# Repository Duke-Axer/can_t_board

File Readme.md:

**Jest to płytka (10 × 10 cm) z procesorem Cortex M0+, zaprojektowana do testów urządzeń komunikujących się przez różne interfejsy.**

## Główne cechy:

**Procesor:** ARM Cortex M0+
**Interfejsy komunikacyjne:**
- SWD (Serial Wire Debug) – programowanie i debugowanie
- SPI (Serial Peripheral Interface)
- UART (Universal Asynchronous Receiver/Transmitter)
- CAN (Controller Area Network)
- USB (Device mode)

**Zasilanie:**
- Wbudowana przetwornica AC/DC
- Zasilanie z gniazda 230 VAC
- Wbudowane napięcia wyjściowe: 5 V i 3.3 V

**Wymiary PCB:** 10 × 10 cm  
**Symulacje:** Przetwornica została zasymulowana w LTspice.  
/projekt  
  ├─ ltspice/         # Symulacje przetwornicy w LTspice  
  ├─ Lib_CAN/      	  # Biblioteka z modelami dla Kicad  
  ├─ BOM/             # Lista użytych footprintów  
  ├─ README.md        # Ten plik  
  └─ CAN_t_b.jpg      # Obraz z widoku 3D

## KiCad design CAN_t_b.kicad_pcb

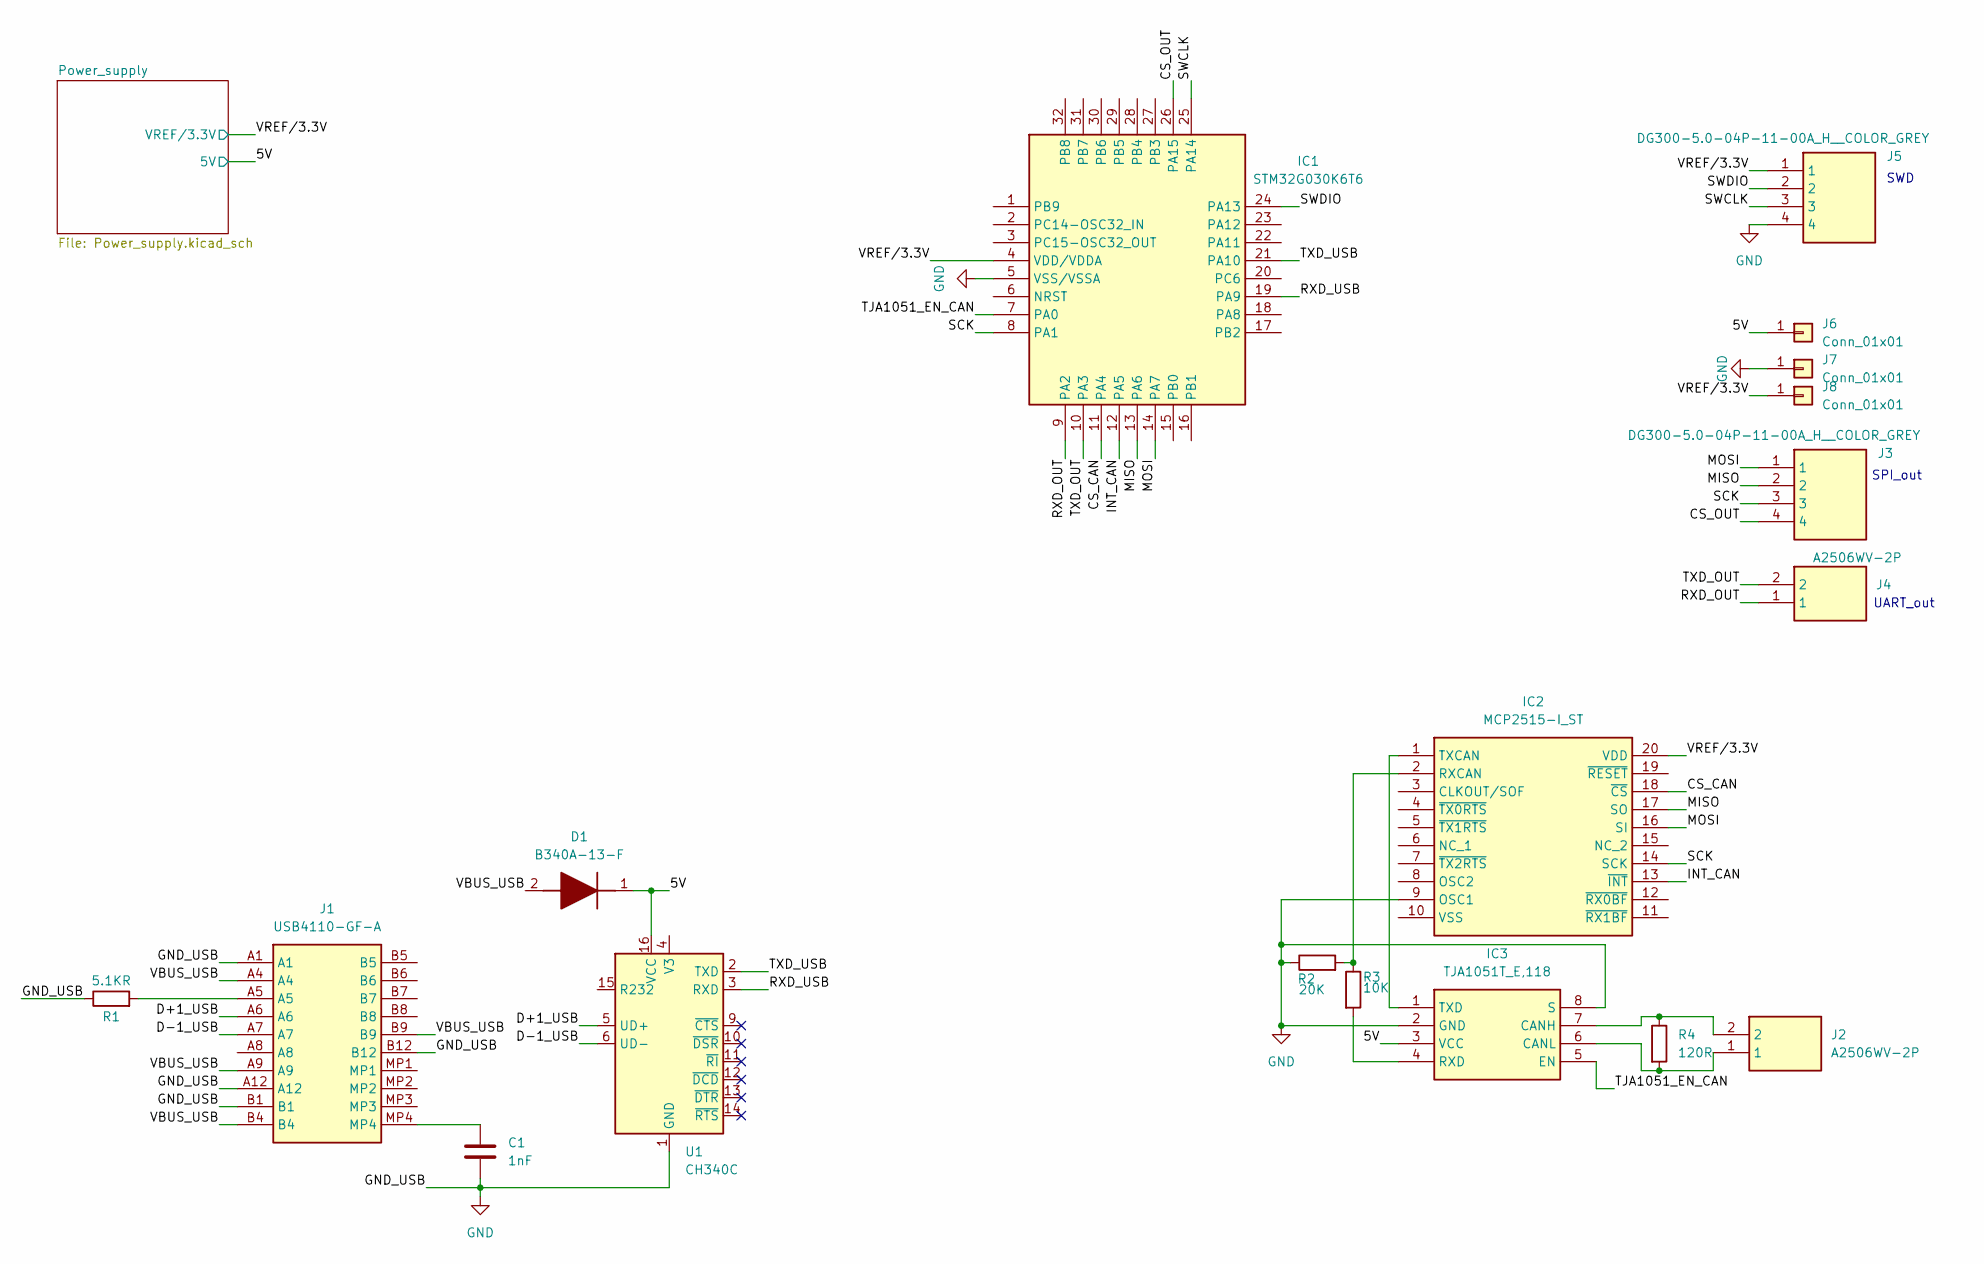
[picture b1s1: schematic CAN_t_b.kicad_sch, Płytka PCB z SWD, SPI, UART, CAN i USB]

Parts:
C1: 1nF; C_0201_0603Metric
D1: B340A-13-F; DIOM5226X240N; Manufacturer_Part_Number B340A-13-F
IC1: STM32G030K6T6; QFP80P900X900X160-32N; Manufacturer_Part_Number STM32G030K6T6
IC2: MCP2515-I_ST; SOP65P640X120-20N; Mouser Part Number 579-MCP2515-I/ST
IC3: TJA1051T_E,118; SOIC127P600X175-8N; Manufacturer_Part_Number TJA1051T/E,118
J1: USB4110-GF-A; USB4110GFA; Manufacturer_Part_Number USB4110-GF-A
J2, J4: A2506WV-2P; A2506WV2P; Manufacturer_Part_Number A2506WV-2P
J3, J5: DG300-5.0-04P-11-00A_H__COLOR_GREY; DG3005004P1100AHCOLORGREY; Manufacturer_Part_Number DG300-5.0-04P-11-00A(H) COLOR GREY
J6, J7, J8: Conn_01x01; PinHeader_1x01_P2.54mm_Vertical
R1: 5.1KR; R_0603_1608Metric
R2: 20K; R_0201_0603Metric
R3: 10K; R_0201_0603Metric
R4: 120R; R_0201_0603Metric
U1: CH340C; SOIC-16_3.9x9.9mm_P1.27mm

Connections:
/5V: D1.1 (K), IC3.3 (VCC), J6.1, U1.16 (VCC); also elsewhere on the board
/CS_CAN: IC1.11 (PA4), IC2.18 (~CS)
/CS_OUT: IC1.26 (PA15), J3.4
/D+1_USB: J1.A6, U1.5 (UD+)
/D-1_USB: J1.A7, U1.6 (UD-)
/INT_CAN: IC1.12 (PA5), IC2.13 (~INT)
/MISO: IC1.13 (PA6), IC2.17 (SO), J3.2
/MOSI: IC1.14 (PA7), IC2.16 (SI), J3.1
/RXD_OUT: IC1.9 (PA2), J4.1
/RXD_USB: IC1.19 (PA9), U1.3 (RXD)
/SCK: IC1.8 (PA1), IC2.14 (SCK), J3.3
/SWCLK: IC1.25 (PA14), J5.3
/SWDIO: IC1.24 (PA13), J5.2
/TJA1051_EN_CAN: IC1.7 (PA0), IC3.5 (EN)
/TXD_OUT: IC1.10 (PA3), J4.2
/TXD_USB: IC1.21 (PA10), U1.2 (TXD)
/VBUS_USB: D1.2 (A), J1.A4, J1.A9, J1.B4, J1.B9
/VREF/3.3V: IC1.4 (VDD/VDDA), IC2.20 (VDD), J5.1, J8.1; also elsewhere on the board
GND: C1.2, IC1.5 (VSS/VSSA), IC2.9 (OSC1), IC3.2 (GND), IC3.8 (S), J1.A1, J1.A12, J1.B1, J1.B12, J5.4, J7.1, R1.1, R2.1, U1.1 (GND); also elsewhere on the board
unnamed: C1.1, J1.MP4
unnamed: IC2.2 (RXCAN), R2.2, R3.1
unnamed: IC2.1 (TXCAN), IC3.1 (TXD)
unnamed: IC3.7 (CANH), J2.2, R4.1
unnamed: IC3.6 (CANL), J2.1, R4.2
unnamed: IC3.4 (RXD), R3.2
unnamed: J1.A5, R1.2

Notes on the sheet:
UART_out
SWD
SPI_out

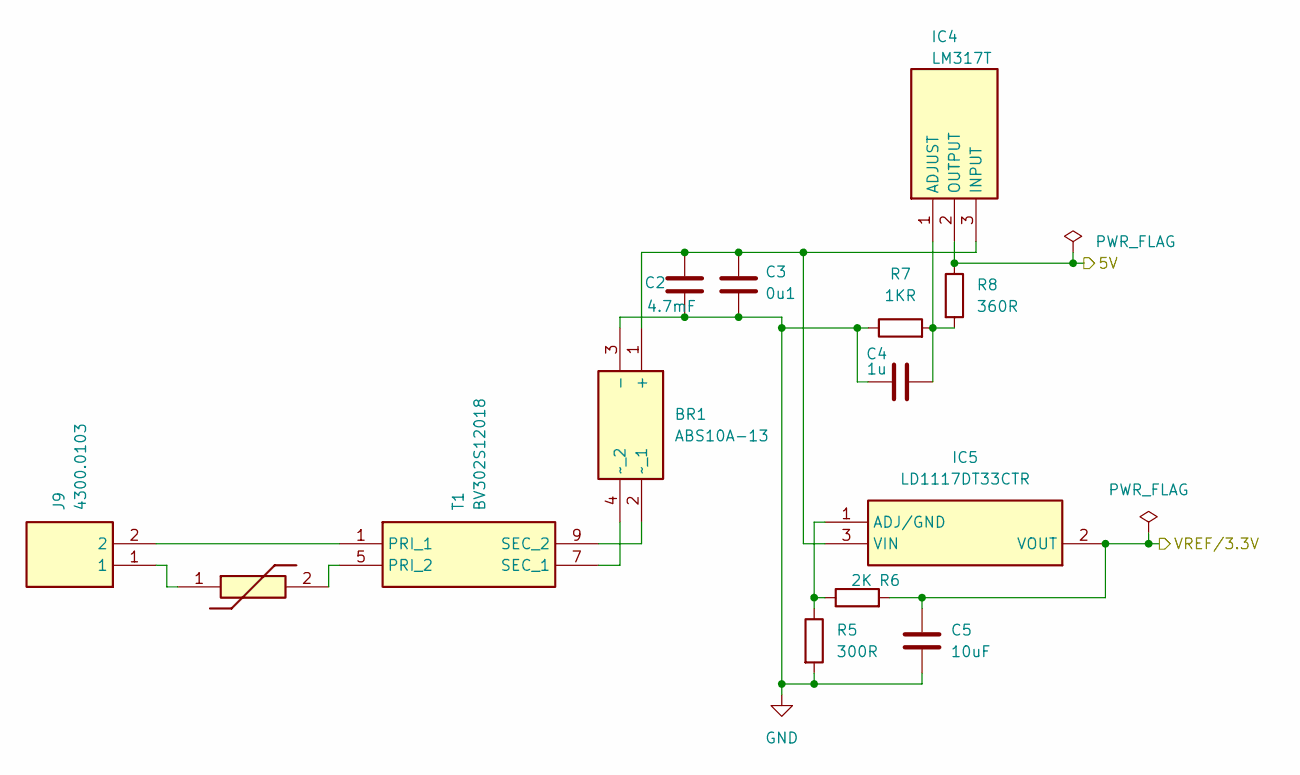
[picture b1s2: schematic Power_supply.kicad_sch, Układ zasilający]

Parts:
BR1: ABS10A-13; ABS10A13; Manufacturer_Part_Number ABS10A-13
C2: 4.7mF; C_Radial_D12.5mm_H25.0mm_P5.00mm
C3: 0u1; C_0402_1005Metric
C4: 1u; C_0201_0603Metric
C5: 10uF; C_1206_3216Metric
IC4: LM317T; TO255P460X1020X2008-3P; Manufacturer_Part_Number LM317T
IC5: LD1117DT33CTR; Manufacturer_Part_Number LD1117DT33CTR
J9: 4300.0103; 43000103; Manufacturer_Part_Number 4300.0103
R5: 300R; R_0201_0603Metric
R6: 2K; R_0603_1608Metric
R7: 1KR; R_0201_0603Metric
R8: 360R; R_0603_1608Metric
RV1: B72220S0271K101; Manufacturer_Part_Number B72220S0271K101
T1: BV302S12018; Manufacturer_Part_Number BV302S12018

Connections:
/5V: IC4.2 (OUTPUT), R8.1; also elsewhere on the board
/VREF/3.3V: C5.1, IC5.2 (VOUT), R6.2; also elsewhere on the board
GND: BR1.3 (-), C2.2, C3.2, C4.1, C5.2, R5.2, R7.1; also elsewhere on the board
unnamed: BR1.1 (+), C2.1, C3.1, IC4.3 (INPUT), IC5.3 (VIN)
unnamed: BR1.2 (~_1), T1.9 (SEC_2)
unnamed: BR1.4 (~_2), T1.7 (SEC_1)
unnamed: C4.2, IC4.1 (ADJUST), R7.2, R8.2
unnamed: IC5.1 (ADJ/GND), R5.1, R6.1
unnamed: J9.1, RV1.1
unnamed: J9.2, T1.1 (PRI_1)
unnamed: RV1.2, T1.5 (PRI_2)

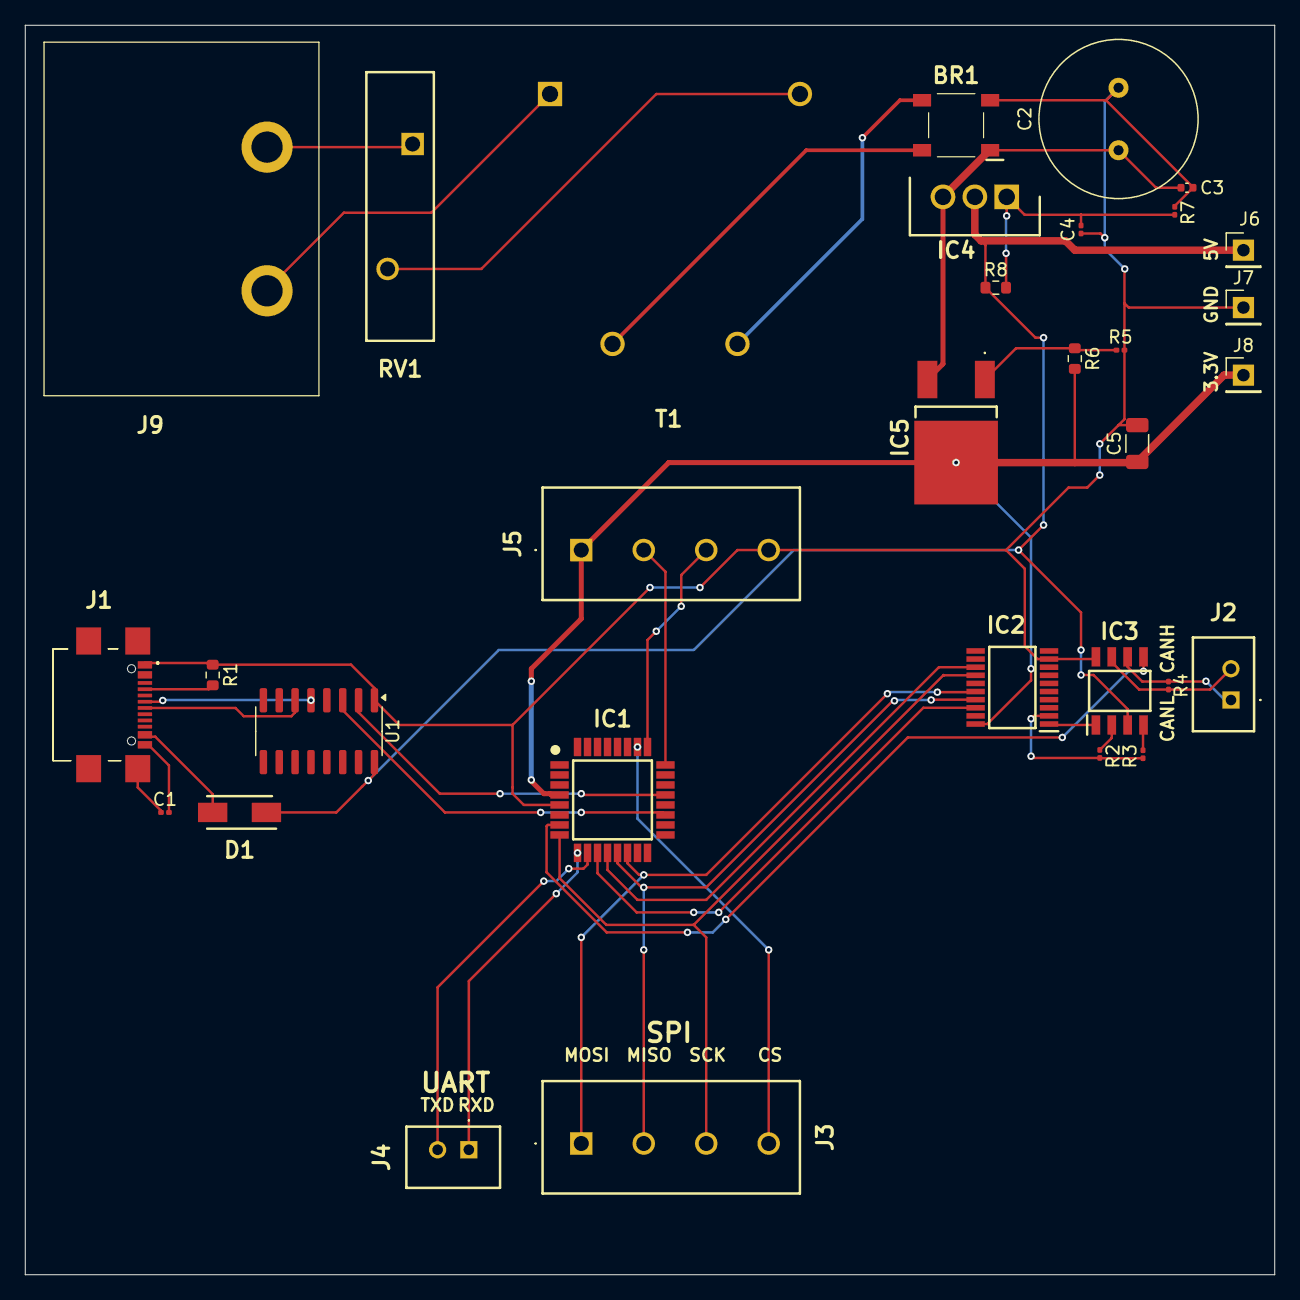
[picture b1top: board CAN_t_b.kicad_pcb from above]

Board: 2 copper layers, 100.0 x 100.0 mm, 32 parts (1 on the bottom side), 34 nets.

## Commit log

2025-09-06 inicjalizacja
2025-09-06 Projekt
2025-09-06 dodanie Readme.md
